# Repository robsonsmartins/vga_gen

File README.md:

## VGA Generator

VGA Generator.

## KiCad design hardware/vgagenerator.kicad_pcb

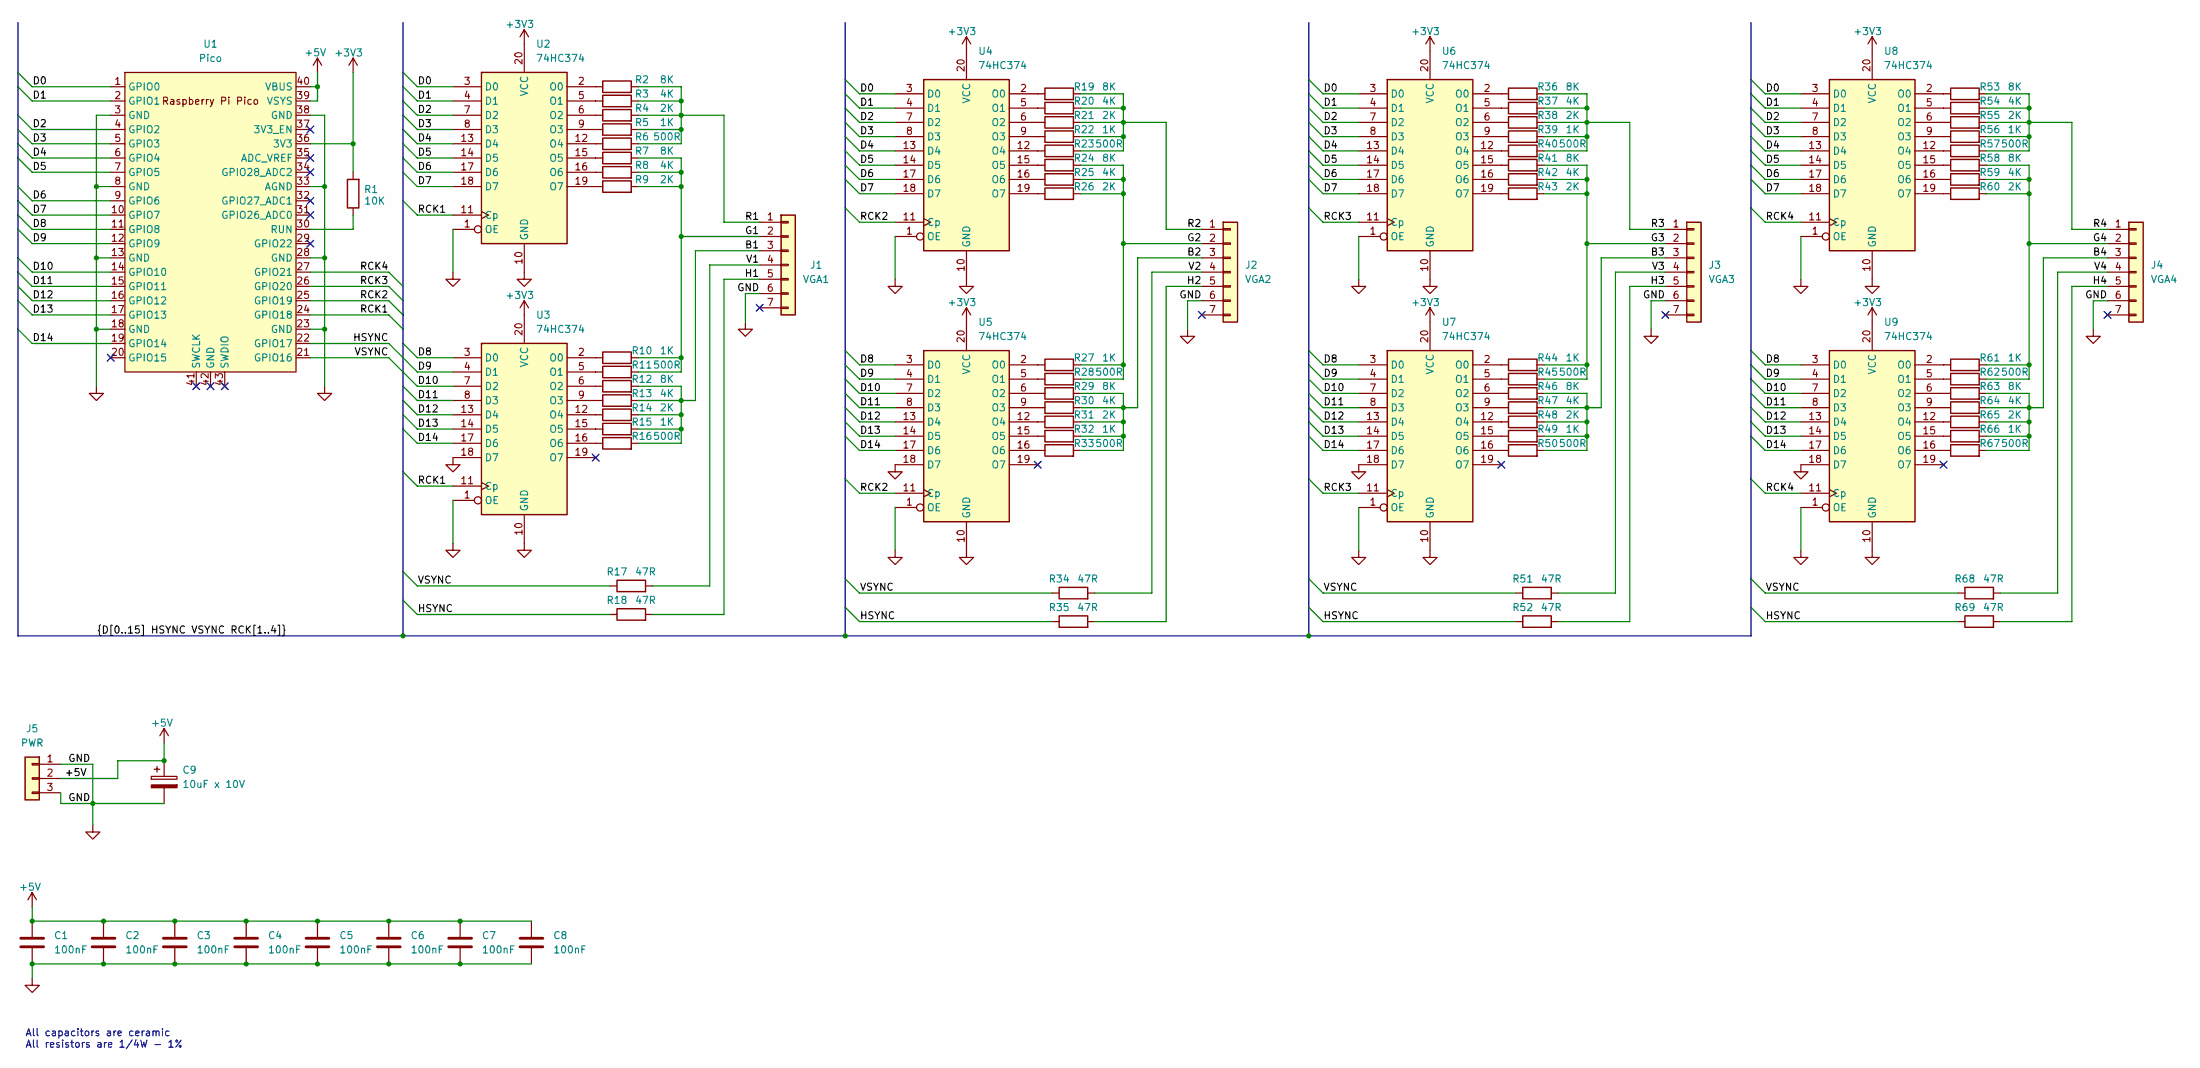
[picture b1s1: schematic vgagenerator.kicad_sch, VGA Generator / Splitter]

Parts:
C1, C2, C3, C4, C5, C6, C7, C8: 100nF; C_Disc_D10.0mm_W2.5mm_P5.00mm
C9: 10uF x 10V; C_Radial_D6.3mm_H11.0mm_P2.50mm
J1: VGA1; PinSocket_1x07_P2.54mm_Vertical
J2: VGA2; PinSocket_1x07_P2.54mm_Vertical
J3: VGA3; PinSocket_1x07_P2.54mm_Vertical
J4: VGA4; PinSocket_1x07_P2.54mm_Vertical
J5: PWR; PinHeader_1x03_P2.54mm_Vertical
R1: 10K; R_Axial_DIN0207_L6.3mm_D2.5mm_P10.16mm_Horizontal
R2, R7, R12, R19, R24, R29, R36, R41, R46, R53, R58, R63: 8K; R_Axial_DIN0207_L6.3mm_D2.5mm_P10.16mm_Horizontal
R3, R8, R13, R20, R25, R30, R37, R42, R47, R54, R59, R64: 4K; R_Axial_DIN0207_L6.3mm_D2.5mm_P10.16mm_Horizontal
R4, R9, R14, R21, R26, R31, R38, R43, R48, R55, R60, R65: 2K; R_Axial_DIN0207_L6.3mm_D2.5mm_P10.16mm_Horizontal
R5, R10, R15, R22, R27, R32, R39, R44, R49, R56, R61, R66: 1K; R_Axial_DIN0207_L6.3mm_D2.5mm_P10.16mm_Horizontal
R6, R11, R16, R23, R28, R33, R40, R45, R50, R57, R62, R67: 500R; R_Axial_DIN0207_L6.3mm_D2.5mm_P10.16mm_Horizontal
R17, R18, R34, R35, R51, R52, R68, R69: 47R; R_Axial_DIN0207_L6.3mm_D2.5mm_P10.16mm_Horizontal
U1: Pico; RPi_Pico_SMD_TH
U2, U3, U4, U5, U6, U7, U8, U9: 74HC374; DIP-20_W7.62mm_LongPads

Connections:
+3V3: R1.2, U1.36 (3V3), U2.20 (VCC), U3.20 (VCC), U4.20 (VCC), U5.20 (VCC), U6.20 (VCC), U7.20 (VCC), U8.20 (VCC), U9.20 (VCC)
+5V: C1.1, C2.1, C3.1, C4.1, C5.1, C6.1, C7.1, C8.1, C9.1, J5.2, U1.39 (VSYS), U1.40 (VBUS)
/B1: J1.3, R12.2, R13.2, R14.2, R15.2, R16.2
/B2: J2.3, R29.2, R30.2, R31.2, R32.2, R33.2
/B3: J3.3, R46.2, R47.2, R48.2, R49.2, R50.2
/B4: J4.3, R63.2, R64.2, R65.2, R66.2, R67.2
/D0: U1.1 (GPIO0), U2.3 (D0), U4.3 (D0), U6.3 (D0), U8.3 (D0)
/D1: U1.2 (GPIO1), U2.4 (D1), U4.4 (D1), U6.4 (D1), U8.4 (D1)
/D2: U1.4 (GPIO2), U2.7 (D2), U4.7 (D2), U6.7 (D2), U8.7 (D2)
/D3: U1.5 (GPIO3), U2.8 (D3), U4.8 (D3), U6.8 (D3), U8.8 (D3)
/D4: U1.6 (GPIO4), U2.13 (D4), U4.13 (D4), U6.13 (D4), U8.13 (D4)
/D5: U1.7 (GPIO5), U2.14 (D5), U4.14 (D5), U6.14 (D5), U8.14 (D5)
/D6: U1.9 (GPIO6), U2.17 (D6), U4.17 (D6), U6.17 (D6), U8.17 (D6)
/D7: U1.10 (GPIO7), U2.18 (D7), U4.18 (D7), U6.18 (D7), U8.18 (D7)
/D8: U1.11 (GPIO8), U3.3 (D0), U5.3 (D0), U7.3 (D0), U9.3 (D0)
/D9: U1.12 (GPIO9), U3.4 (D1), U5.4 (D1), U7.4 (D1), U9.4 (D1)
/D10: U1.14 (GPIO10), U3.7 (D2), U5.7 (D2), U7.7 (D2), U9.7 (D2)
/D11: U1.15 (GPIO11), U3.8 (D3), U5.8 (D3), U7.8 (D3), U9.8 (D3)
/D12: U1.16 (GPIO12), U3.13 (D4), U5.13 (D4), U7.13 (D4), U9.13 (D4)
/D13: U1.17 (GPIO13), U3.14 (D5), U5.14 (D5), U7.14 (D5), U9.14 (D5)
/D14: U1.19 (GPIO14), U3.17 (D6), U5.17 (D6), U7.17 (D6), U9.17 (D6)
/G1: J1.2, R7.2, R8.2, R9.2, R10.2, R11.2
/G2: J2.2, R24.2, R25.2, R26.2, R27.2, R28.2
/G3: J3.2, R41.2, R42.2, R43.2, R44.2, R45.2
/G4: J4.2, R58.2, R59.2, R60.2, R61.2, R62.2
/H1: J1.5, R18.2
/H2: J2.5, R35.2
/H3: J3.5, R52.2
/H4: J4.5, R69.2
/HSYNC: R18.1, R35.1, R52.1, R69.1, U1.22 (GPIO17)
/R1: J1.1, R2.2, R3.2, R4.2, R5.2, R6.2
/R2: J2.1, R19.2, R20.2, R21.2, R22.2, R23.2
/R3: J3.1, R36.2, R37.2, R38.2, R39.2, R40.2
/R4: J4.1, R53.2, R54.2, R55.2, R56.2, R57.2
/RCK1: U1.24 (GPIO18), U2.11 (Cp), U3.11 (Cp)
/RCK2: U1.25 (GPIO19), U4.11 (Cp), U5.11 (Cp)
/RCK3: U1.26 (GPIO20), U6.11 (Cp), U7.11 (Cp)
/RCK4: U1.27 (GPIO21), U8.11 (Cp), U9.11 (Cp)
/V1: J1.4, R17.2
/V2: J2.4, R34.2
/V3: J3.4, R51.2
/V4: J4.4, R68.2
/VSYNC: R17.1, R34.1, R51.1, R68.1, U1.21 (GPIO16)
GND: C1.2, C2.2, C3.2, C4.2, C5.2, C6.2, C7.2, C8.2, C9.2, J1.6, J2.6, J3.6, J4.6, J5.1, J5.3, U1.3 (GND), U1.8 (GND), U1.13 (GND), U1.18 (GND), U1.23 (GND), U1.28 (GND), U1.33 (AGND), U1.38 (GND), U2.1 (OE), U2.10 (GND), U3.1 (OE), U3.10 (GND), U3.18 (D7), U4.1 (OE), U4.10 (GND), U5.1 (OE), U5.10 (GND), U5.18 (D7), U6.1 (OE), U6.10 (GND), U7.1 (OE), U7.10 (GND), U7.18 (D7), U8.1 (OE), U8.10 (GND), U9.1 (OE), U9.10 (GND), U9.18 (D7)
unnamed: R1.1, U1.30 (RUN)
unnamed: R2.1, U2.2 (O0)
unnamed: R3.1, U2.5 (O1)
unnamed: R4.1, U2.6 (O2)
unnamed: R5.1, U2.9 (O3)
unnamed: R6.1, U2.12 (O4)
unnamed: R7.1, U2.15 (O5)
unnamed: R8.1, U2.16 (O6)
unnamed: R9.1, U2.19 (O7)
unnamed: R10.1, U3.2 (O0)
unnamed: R11.1, U3.5 (O1)
unnamed: R12.1, U3.6 (O2)
unnamed: R13.1, U3.9 (O3)
unnamed: R14.1, U3.12 (O4)
unnamed: R15.1, U3.15 (O5)
unnamed: R16.1, U3.16 (O6)
unnamed: R19.1, U4.2 (O0)
unnamed: R20.1, U4.5 (O1)
unnamed: R21.1, U4.6 (O2)
unnamed: R22.1, U4.9 (O3)
unnamed: R23.1, U4.12 (O4)
unnamed: R24.1, U4.15 (O5)
unnamed: R25.1, U4.16 (O6)
unnamed: R26.1, U4.19 (O7)
unnamed: R27.1, U5.2 (O0)
unnamed: R28.1, U5.5 (O1)
unnamed: R29.1, U5.6 (O2)
unnamed: R30.1, U5.9 (O3)
unnamed: R31.1, U5.12 (O4)
unnamed: R32.1, U5.15 (O5)
unnamed: R33.1, U5.16 (O6)
unnamed: R36.1, U6.2 (O0)
unnamed: R37.1, U6.5 (O1)
unnamed: R38.1, U6.6 (O2)
unnamed: R39.1, U6.9 (O3)
unnamed: R40.1, U6.12 (O4)
unnamed: R41.1, U6.15 (O5)
unnamed: R42.1, U6.16 (O6)
unnamed: R43.1, U6.19 (O7)
unnamed: R44.1, U7.2 (O0)
unnamed: R45.1, U7.5 (O1)
unnamed: R46.1, U7.6 (O2)
unnamed: R47.1, U7.9 (O3)
unnamed: R48.1, U7.12 (O4)
unnamed: R49.1, U7.15 (O5)
unnamed: R50.1, U7.16 (O6)
unnamed: R53.1, U8.2 (O0)
unnamed: R54.1, U8.5 (O1)
unnamed: R55.1, U8.6 (O2)
unnamed: R56.1, U8.9 (O3)
unnamed: R57.1, U8.12 (O4)
unnamed: R58.1, U8.15 (O5)
unnamed: R59.1, U8.16 (O6)
unnamed: R60.1, U8.19 (O7)
unnamed: R61.1, U9.2 (O0)
unnamed: R62.1, U9.5 (O1)
unnamed: R63.1, U9.6 (O2)
unnamed: R64.1, U9.9 (O3)
unnamed: R65.1, U9.12 (O4)
unnamed: R66.1, U9.15 (O5)
unnamed: R67.1, U9.16 (O6)

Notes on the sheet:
All capacitors are ceramic All resistors are 1/4W - 1%

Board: 2 copper layers, 92 parts (0 on the bottom side), 105 nets, no tracks yet.

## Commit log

2022-12-12 Created schematic
2022-12-12 Updated schematic
2022-12-14 Updated schematics
